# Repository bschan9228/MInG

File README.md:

# MInG
MInG is a hardware password manager. More information can be found below: 

https://bschan9228.github.io/MInG/

https://docs.google.com/document/d/1XQeUcRW4mPYvgZ0W_UPjm9wVBVjZgWeWX6C9jlaiZSg/edit

## Folder Structure
    .
    ├── Hardware                # Project hardware and PCB
    │   ├── Final               # Final PCB 
    │   └── Prototype           # Prototype PCB's
    └── Software
            ├── Experimental    # Experimental firmware for the device
            └── Final           # Final firmware for the device

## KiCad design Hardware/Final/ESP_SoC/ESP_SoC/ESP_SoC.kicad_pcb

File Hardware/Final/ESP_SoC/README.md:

# Final PCB
Final PCB design for the ESP32 PCB. Currently Have not been produced. Includes reverse polarity protection.

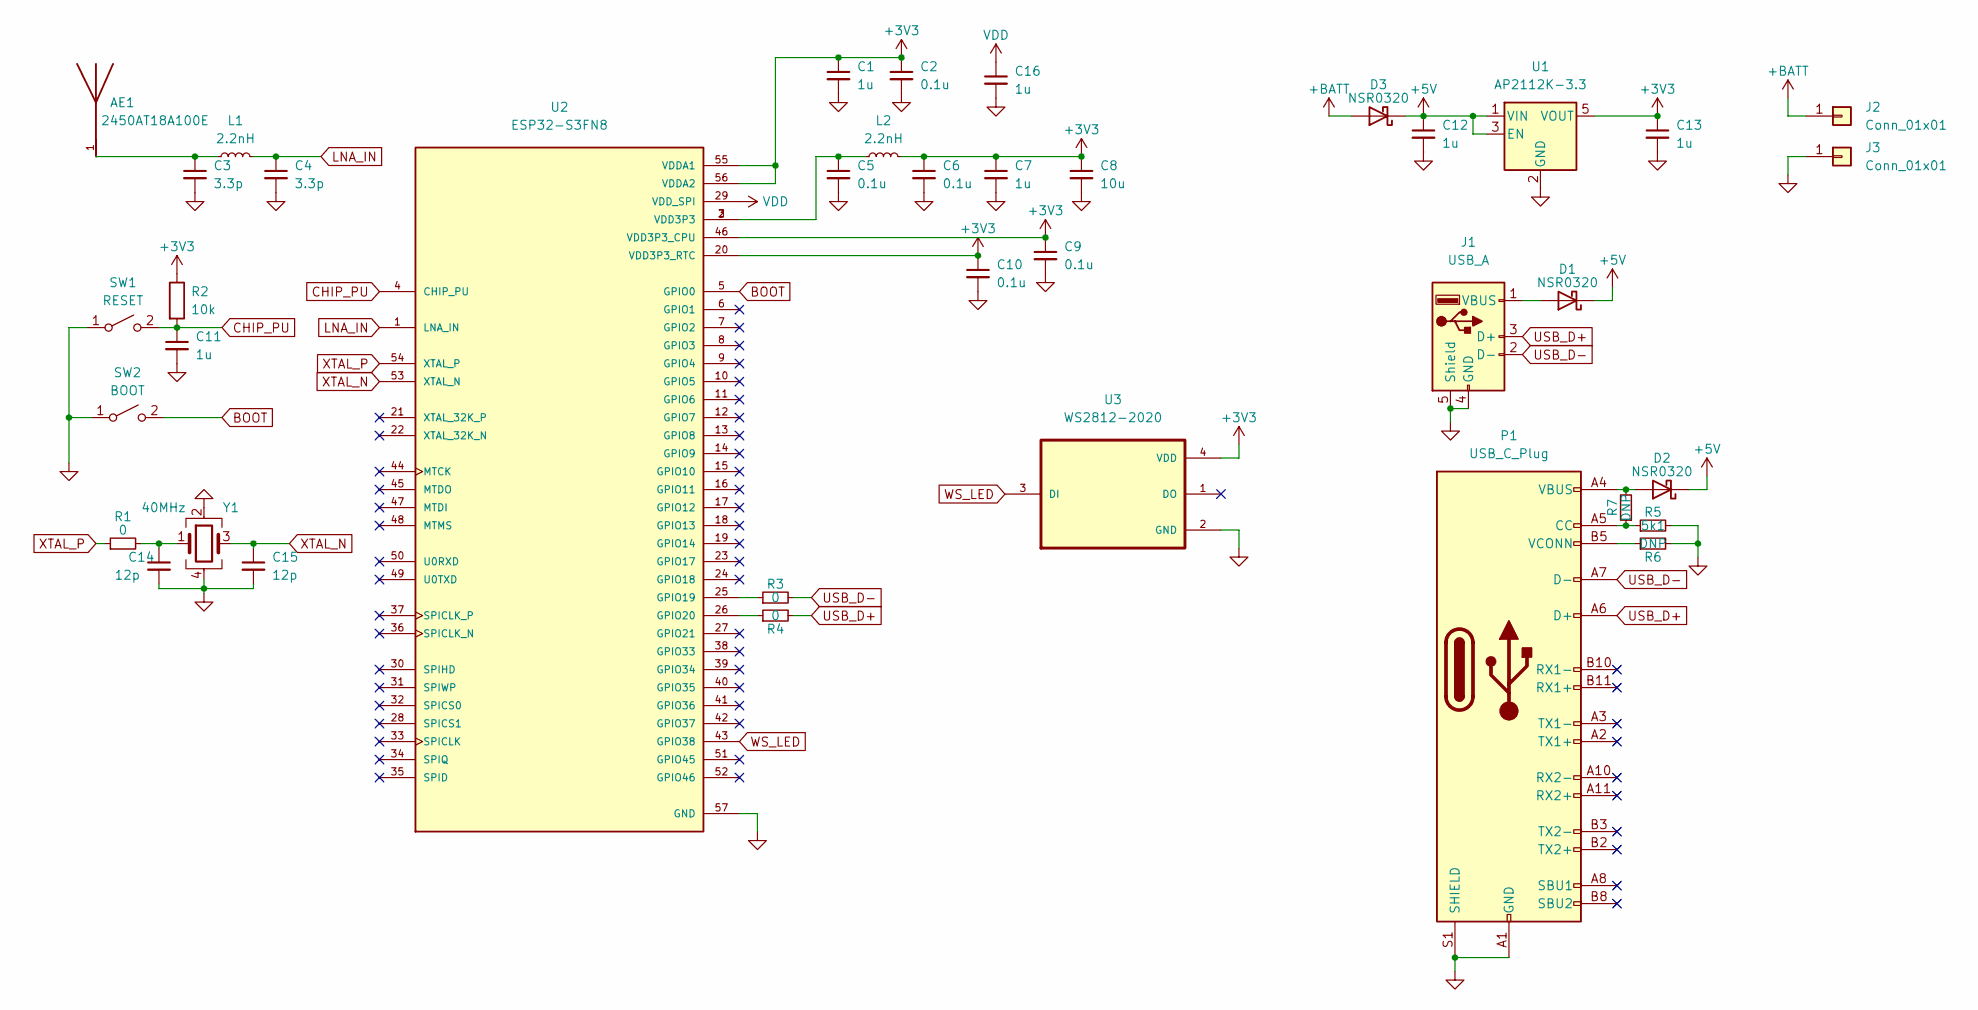
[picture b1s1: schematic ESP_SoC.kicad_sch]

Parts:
AE1: 2450AT18A100E; ANTC3216X140N; PARTREV 1.3; LCSC Part # C89334
C1, C7, C11, C12, C13, C16: 1u; C_0402_1005Metric; LCSC Part # C52923
C2, C5, C6, C9, C10: 0.1u; C_0402_1005Metric; LCSC Part # C307331
C3, C4: 3.3p; C_0402_1005Metric; LCSC Part # C1565
C8: 10u; C_0603_1608Metric; LCSC Part # C19702
C14, C15: 12p; C_0402_1005Metric; LCSC Part # C1547
D1, D2, D3: NSR0320; D_SOD-323F; LCSC Part # C48192
J1: USB_A; USB_A_CNCTech_1001-011-01101_Horizontal; LCSC Part # C283548
J2, J3: Conn_01x01; SolderWirePad_1x01_SMD_1x2mm
L1, L2: 2.2nH; L_0402_1005Metric; LCSC Part # C91240
P1: USB_C_Plug; USB_C_Plug_Molex_105444; LCSC Part # C134082
R1, R3, R4: 0; R_0402_1005Metric; LCSC Part # C17168
R2: 10k; R_0402_1005Metric; LCSC Part # C25744
R5: 5k1; R_0402_1005Metric; LCSC Part # C25905
R6, R7: DNP; R_0402_1005Metric
SW1: RESET; SW_SPST_PTS810; LCSC Part # C221897
SW2: BOOT; SW_SPST_PTS810; LCSC Part # C221897
U1: AP2112K-3.3; SOT-23-5; LCSC Part # C51118
U2: ESP32-S3FN8; QFN40P700X700X90-57N
U3: WS2812-2020; LED_WS2812-2020; PARTREV V1.3; LCSC Part # C2976072
Y1: 40MHz; Crystal_SMD_2016-4Pin_2.0x1.6mm; LCSC Part # C255898

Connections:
+3V3: C1.1, C2.1, C6.1, C7.1, C8.1, C9.1, C10.1, C13.1, L2.2, R2.1, U1.5 (VOUT), U2.20 (VDD3P3_RTC), U2.46 (VDD3P3_CPU), U2.55 (VDDA1), U2.56 (VDDA2), U3.4 (VDD)
+5V: C12.1, D1.1 (K), D2.1 (K), D3.1 (K), U1.1 (VIN), U1.3 (EN)
+BATT: D3.2 (A), J2.1
BOOT: SW2.2 (B), U2.5 (GPIO0)
CHIP_PU: C11.1, R2.2, SW1.2 (B), U2.4 (CHIP_PU)
GND: C1.2, C2.2, C3.2, C4.2, C5.2, C6.2, C7.2, C8.2, C9.2, C10.2, C11.2, C12.2, C13.2, C14.2, C15.2, C16.2, J1.4 (GND), J1.5 (Shield), J3.1, P1.A1 (GND), P1.A12 (GND), P1.B1 (GND), P1.B12 (GND), P1.S1 (SHIELD), R5.2, R6.2, SW1.1 (A), SW2.1 (A), U1.2 (GND), U2.57 (GND), U3.2 (GND), Y1.2, Y1.4
LNA_IN: C4.1, L1.2, U2.1 (LNA_IN)
unnamed: AE1.1, C3.1, L1.1
unnamed: C5.1, L2.1, U2.2 (VDD3P3), U2.3 (VDD3P3)
unnamed: C14.1, R1.2, Y1.1
unnamed: D1.2 (A), J1.1 (VBUS)
unnamed: D2.2 (A), P1.A4 (VBUS), P1.A9 (VBUS), P1.B4 (VBUS), P1.B9 (VBUS), R7.2
unnamed: P1.A5 (CC), R5.1, R7.1
unnamed: P1.B5 (VCONN), R6.1
unnamed: R3.1, U2.25 (GPIO19)
unnamed: R4.1, U2.26 (GPIO20)
USB_D+: J1.3 (D+), P1.A6 (D+), R4.2
USB_D-: J1.2 (D-), P1.A7 (D-), R3.2
VDD: C16.1, U2.29 (VDD_SPI)
WS_LED: U2.43 (GPIO38), U3.3 (DI)
XTAL_N: C15.1, U2.53 (XTAL_N), Y1.3
XTAL_P: R1.1, U2.54 (XTAL_P)

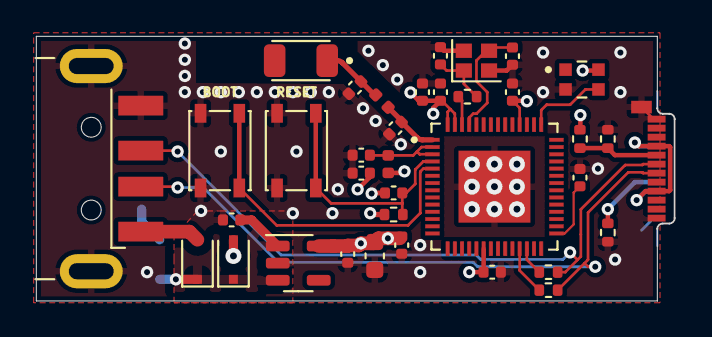
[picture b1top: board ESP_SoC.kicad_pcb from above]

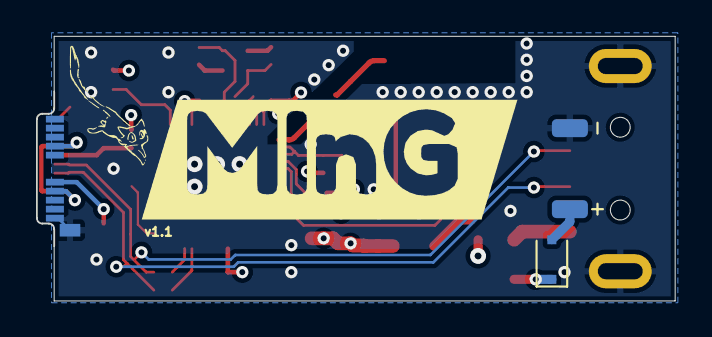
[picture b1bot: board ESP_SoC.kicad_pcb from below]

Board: 4 copper layers, 35.5 x 14.7 mm, 40 parts (4 on the bottom side), 22 nets.

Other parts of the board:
kibuzzard-64092D35: G***; kibuzzard-64092D35

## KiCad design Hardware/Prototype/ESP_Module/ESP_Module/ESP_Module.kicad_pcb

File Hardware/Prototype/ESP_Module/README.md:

# Module
Working ESP32-S3 Module USB-A device.

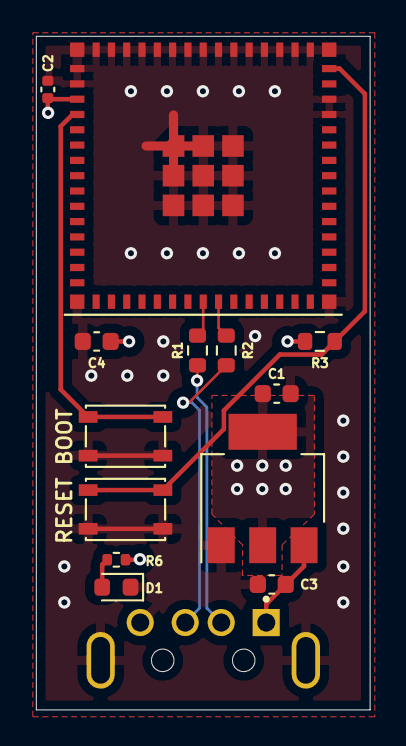
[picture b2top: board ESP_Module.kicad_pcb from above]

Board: 4 copper layers, 18.5 x 37.4 mm, 14 parts (0 on the bottom side), 10 nets.

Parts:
C1, C3, C4: 22u; C_0603_1608Metric
C2: .1u; C_0402_1005Metric
D1: LED; LED_0603_1608Metric
J1: 48037-0001; MOLEX_48037-0001
R1, R2: 0; R_0603_1608Metric
R3: 10k; R_0603_1608Metric
R6: 5k1; R_0402_1005Metric
SW1, SW2: SW_SPST; SW_SPST_PTS810
U1: AMS1117-3.3; SOT-223-3_TabPin2
U2: ESP32-S3-MINI-1-N8; XCVR_ESP32-S3-MINI-1-N8

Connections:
+3V3: C1.1, C2.1, C4.1, R3.1, R6.1, U1.2 (VO), U2.3 (3V3)
+5V: C3.1, J1.1 (VCC), U1.3 (VI)
/MCU_D+: R2.1, U2.24 (IO20)
/MCU_D-: R1.1, U2.23 (IO19)
GND: C1.2, C2.2, C3.2, C4.2, D1.1 (K), J1.4 (GND), J1.S1 (SHIELD), J1.S2 (SHIELD), SW1.2 (B), SW2.2 (B), U1.1 (GND), U2.1 (GND), U2.2 (GND), U2.42 (GND), U2.43 (GND), U2.46 (GND), U2.47 (GND), U2.48 (GND), U2.49 (GND), U2.50 (GND), U2.51 (GND), U2.52 (GND), U2.53 (GND), U2.54 (GND), U2.55 (GND), U2.56 (GND), U2.57 (GND), U2.58 (GND), U2.59 (GND), U2.60 (GND), U2.61 (GND), U2.61_1 (GND), U2.61_2 (GND), U2.61_3 (GND), U2.61_4 (GND), U2.61_5 (GND), U2.61_6 (GND), U2.61_7 (GND), U2.61_8 (GND), U2.62 (GND), U2.63 (GND), U2.64 (GND), U2.65 (GND)
MCU_BOOT: SW2.1 (A), U2.4 (IO0)
MCU_EN: R3.2, SW1.1 (A), U2.45 (EN)
unnamed: D1.2 (A), R6.2
USB_D+: J1.3 (D+), R2.2
USB_D-: J1.2 (D-), R1.2

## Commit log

2023-02-04 Initialized directories
2023-02-05 Added prototyped boards
2023-02-05 Finished prototyped module
2023-02-08 Added ESP SoC PCB Files
2023-02-10 Finished PCB prototypes and BOM
2023-02-12 Added website files
2023-02-12 Added website folder
2023-02-14 Added website
2023-02-14 redirect
2023-02-15 Added some software for access point and http
2023-02-15 Added ap + ws
2023-02-16 Implemented ap + ws + usb hid backend
2023-02-16 Added keyboard hid + ws
2023-02-17 ws + keyboard w/simple html ui
2023-02-17 Integrated ws + json
2023-02-17 Built half working keyboard
2023-02-19 Fixed HID input + began pm
2023-02-19 Made pm clickable
2023-02-20 pm w/o nvs
2023-02-21 pm + fatfs
2023-02-22 Fixed keyboard
2023-02-22 Added partitions
2023-02-27 add a multiple choice button
2023-02-27 add button for all html
2023-03-02 add content in worshop
2023-03-02 update some photos and pcb info
2023-03-07 update references
2023-03-07 correction for website link
2023-03-08 implementing ui for pm and delete
2023-03-08 fixed delete, still needs to reload
2023-03-08 reseting fields after saving
2023-03-09 fixed form
2023-03-11 Added final PCB design
2023-03-13 config ability
2023-03-14 Added default credentials
2023-03-14 Finalized and added SSID config
2023-03-14 update photo and poster
2023-03-18 video and pics
2023-03-18 info
2023-03-18 workshop doc link
